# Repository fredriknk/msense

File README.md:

# Methanesense

 <!-- 3D rendered pretty view -->

Open Source hardware kicad source files for a NRF9160 based methane sensor utilizing MOX sensor.

Low power design with about 60ua average current consumption measuring Methane, temp, pressure and humidity every 30 seconds, averaging values over 5 minute samples, and transmitting 11 readings every 55 minutes. estimated battery life is 4.5 years from a 3200mah  18650 liion cell

It has an option for a GPS if necessary, but this will cause reduced battery life. 

[Assembly IBOM](https://htmlpreview.github.io/?https://raw.githubusercontent.com/fredriknk/Methanesense/main/DOCUMENTATION/ibom.html) <!-- Interactive BOM PDF -->

[PCB layout](./DOCUMENTATION/Methanesense_board_prints.pdf) <!-- PDFs of boards -->

[SCHEMATIC](./DOCUMENTATION/Methanesense_schematic.pdf) <!-- Schematic PDFs -->

## FRONT

## BACK

## SIDE

## Enclosure
Enclosure proposal. Simple 3d printed design snap lock, potential for epoxy fill for moisture resistance. But for now i just coat them in PLASTIK 70 conformal coating by Kontakt Chemie. DO REMEMBER TO SEAL SENSOR HOLES!!!

When 3d printing the enclosure, modify the two boxes in the sensor holes to be printed with gyroid infill with no walls or top/bottom to create the mesh. Enclosure files are in the [3D_MODEL](./3D_MODEL/) folder.

## Documentation

[NRF9160SOC](./DOCUMENTATION/Datasheets/nRF9160_PS_v2.0.pdf)

[ADC](./DOCUMENTATION/Datasheets/ads1113.pdf)

[Temp/press/humidity sensor](./DOCUMENTATION/Datasheets/bst-bme680-ds001.pdf)

[Powersupply PMIC](./DOCUMENTATION/Datasheets/nPM1300_PS_v1.0.pdf)

[MOX Sensor](./DOCUMENTATION/Datasheets/tgs8410_product_infomation(en)_rev05.pdf)

# Before major commmits
Remember to run generate_outputs.bat/sh
to update the outputs and pictures.
readmetemplate

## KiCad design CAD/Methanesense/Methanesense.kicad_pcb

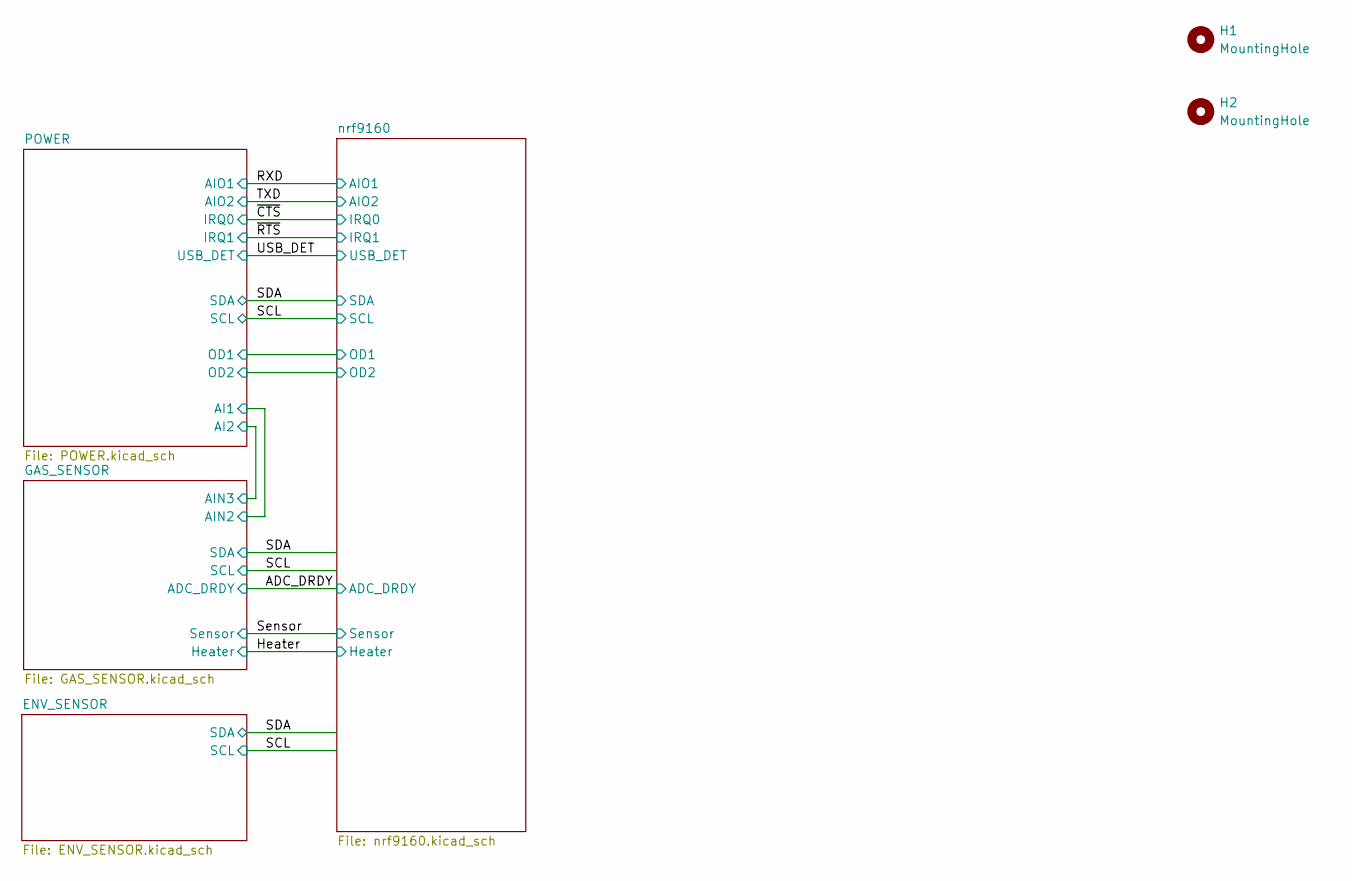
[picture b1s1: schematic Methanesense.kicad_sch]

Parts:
H1, H2: MountingHole; MountingHole_2.2mm_M2

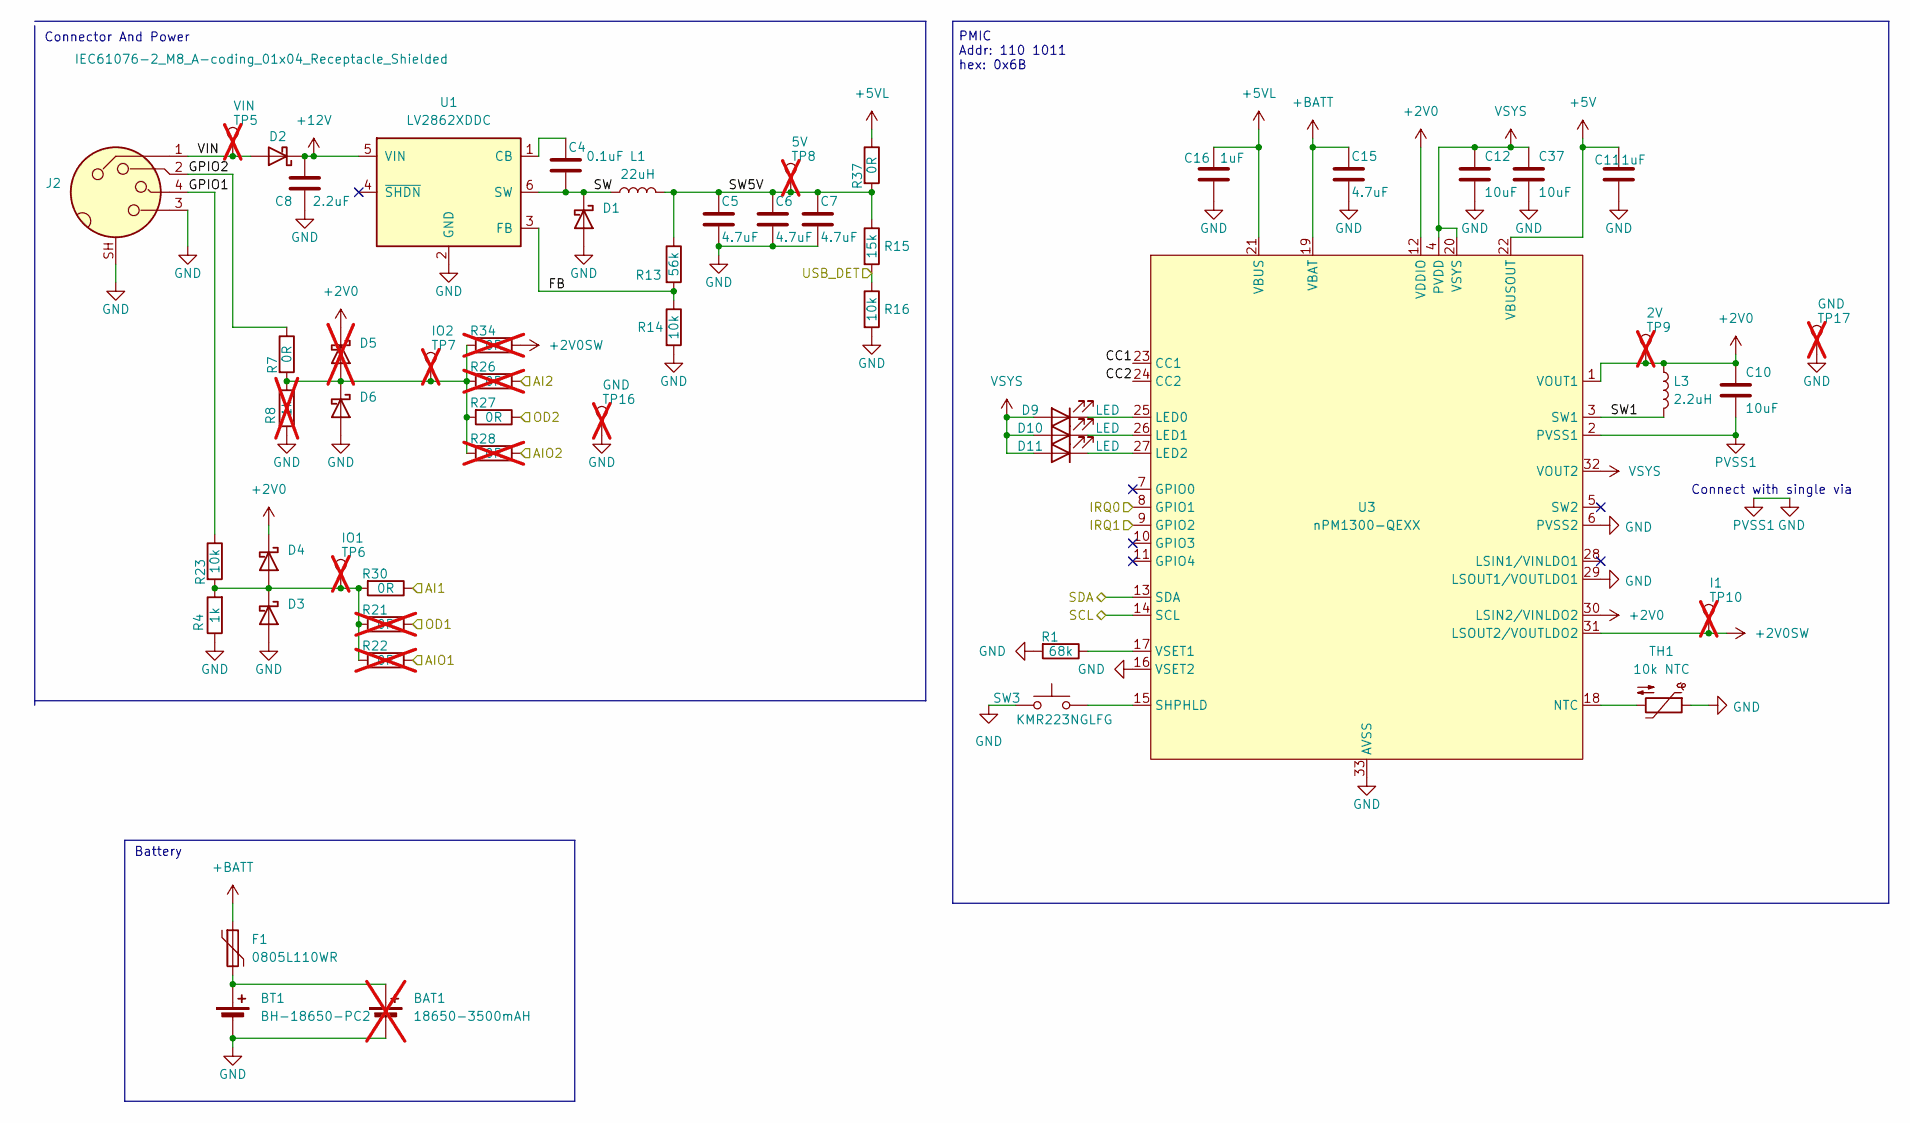
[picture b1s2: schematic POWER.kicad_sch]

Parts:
BAT1: 18650-3500mAH; not fitted
BT1: BH-18650-PC2; BatteryHolder_MPD_BH-18650-PC2; MPN BH-18650-PC2
C4: 0.1uF; C_0603_1608Metric
C5, C6, C7, C15: 4.7uF; C_0603_1608Metric
C8: 2.2uF; C_0805_2012Metric
C10, C12, C37: 10uF; C_0805_2012Metric
C11, C16: 1uF; C_0603_1608Metric
D1, D2: MSS1P3L-M3/89A; D_MicroSMP_AK; MPN MSS1P3L-M3/89A
D3, D4, D6: SD0603S040S0R2; D_0603_1608Metric; MPN SD0603S040S0R2
D5: SD0603S040S0R2; D_0603_1608Metric; MPN SD0603S040S0R2; not fitted
D9, D10, D11: LED; LED_0603_1608Metric; MPN LG L29K-G2J1-24-Z
F1: 0805L110WR; Fuse_0805_2012Metric; MPN 0805L110WR
J2: IEC61076-2_M8_A-coding_01x04_Receptacle_Shielded; STEWART_SS-12800-004_M8_04_Socket_Right_Angle; MPN SS-12800-004
L1: 22uH; L_Abracon_AMDLA4020S; MPN AMDLA4020S-220MT
L3: 2.2uH; L_1008_2520Metric; MPN CVH252009-2R2M
R1: 68k; R_0603_1608Metric
R4: 1k; R_0603_1608Metric
R7, R27, R30, R37: 0R; R_0603_1608Metric
R8: 1k; R_0603_1608Metric; not fitted
R13: 56k; R_0603_1608Metric
R14, R16, R23: 10k; R_0603_1608Metric
R15: 15k; R_0603_1608Metric
R21, R22, R26, R28, R34: 0R; R_0603_1608Metric; not fitted
SW3: KMR223NGLFG; SW_Push_1P1T_NO_CK_KMR2; MPN KMR223GLFG
TH1: 10k NTC; R_0603_1608Metric; MPN NTCG163JF103FT1
TP5: VIN; TestPoint_Pad_D1.0mm; not fitted
TP6: IO1; TestPoint_Pad_D1.0mm; not fitted
TP7: IO2; TestPoint_Pad_D1.0mm; not fitted
TP8: 5V; TestPoint_Pad_D1.0mm; not fitted
TP9: 2V; TestPoint_Pad_D1.0mm; not fitted
TP10: I1; TestPoint_Pad_D1.0mm; not fitted
TP16, TP17: GND; TestPoint_Pad_D1.0mm; not fitted
U1: LV2862XDDC; SOT-23-6; MPN LV2862XLVDDCR
U3: nPM1300-QEXX; QFN-32-1EP_5x5mm_P0.5mm_EP3.6x3.6mm_ThermalVias; MPN nPM1300-QEAA-R7

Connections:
+2V0: C10.1, D4.1 (K), D5.1 (K), L3.1, TP9.1, U3.1 (VOUT1), U3.12 (VDDIO), U3.30 (LSIN2/VINLDO2); also elsewhere on the board
+2V0SW: R34.1, TP10.1, U3.31 (LSOUT2/VOUTLDO2)
+5V: C11.1, U3.22 (VBUSOUT)
+5VL: C16.1, R37.1, U3.21 (VBUS)
+12V: C8.1, D2.1 (K), U1.5 (VIN); also elsewhere on the board
+BATT: C15.1, F1.1, U3.19 (VBAT); also elsewhere on the board
/GAS_SENSOR/AIN2: R30.1; also elsewhere on the board
/GAS_SENSOR/AIN3: R26.1; also elsewhere on the board
/POWER/CC1: U3.23 (CC1)
/POWER/CC2: U3.24 (CC2)
/POWER/FB: R13.2, R14.1, U1.3 (FB)
/POWER/GPIO1: J2.4, R23.1
/POWER/GPIO2: J2.2, R7.1
/POWER/OD1: R21.1; also elsewhere on the board
/POWER/OD2: R27.1; also elsewhere on the board
/POWER/SW: C4.2, D1.1 (K), L1.1, U1.6 (SW)
/POWER/SW1: L3.2, U3.3 (SW1)
/POWER/SW5V: C5.1, C6.1, C7.1, L1.2, R13.1, R15.1, R37.2, TP8.1
/POWER/VIN: D2.2 (A), J2.1, TP5.1
GND: BAT1.2 (-), BT1.2 (-), C5.2, C6.2, C7.2, C8.2, C10.2, C11.2, C12.2, C15.2, C16.2, C37.2, D1.2 (A), D3.2 (A), D6.2 (A), J2.3, J2.SH, R1.2, R4.1, R8.1, R14.2, R16.2, SW3.2, TH1.1, TP16.1, TP17.1, U1.2 (GND), U3.2 (PVSS1), U3.6 (PVSS2), U3.16 (VSET2), U3.29 (LSOUT1/VOUTLDO1), U3.33 (AVSS); also elsewhere on the board
unnamed: BAT1.1 (+), BT1.1 (+), F1.2
unnamed: D3.1 (K), D4.2 (A), R4.2, R21.2, R22.2, R23.2, R30.2, TP6.1
unnamed: D5.2 (A), D6.1 (K), R7.2, R8.2, R26.2, R27.2, R28.2, R34.2, TP7.1
unnamed: D9.1 (K), U3.25 (LED0)
unnamed: D10.1 (K), U3.26 (LED1)
unnamed: D11.1 (K), U3.27 (LED2)
unnamed: C4.1, U1.1 (CB)
unnamed: TH1.2, U3.18 (NTC)
unnamed: SW3.1, U3.15 (SHPHLD)
unnamed: R1.1, U3.17 (VSET1)
P0.05: R15.2, R16.1; also elsewhere on the board
P0.11: U3.8 (GPIO1); also elsewhere on the board
P0.12: U3.9 (GPIO2); also elsewhere on the board
P0.15/AIN2: R28.1; also elsewhere on the board
P0.16/AIN3: R22.1; also elsewhere on the board
P0.28: U3.13 (SDA); also elsewhere on the board
P0.29: U3.14 (SCL); also elsewhere on the board
VCC: C12.1, C37.1, D9.2 (A), D10.2 (A), D11.2 (A), U3.4 (PVDD), U3.20 (VSYS), U3.32 (VOUT2); also elsewhere on the board

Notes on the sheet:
Connect with single via
Addr: 110 1011 hex: 0x6B
Connector And Power
PMIC
Battery

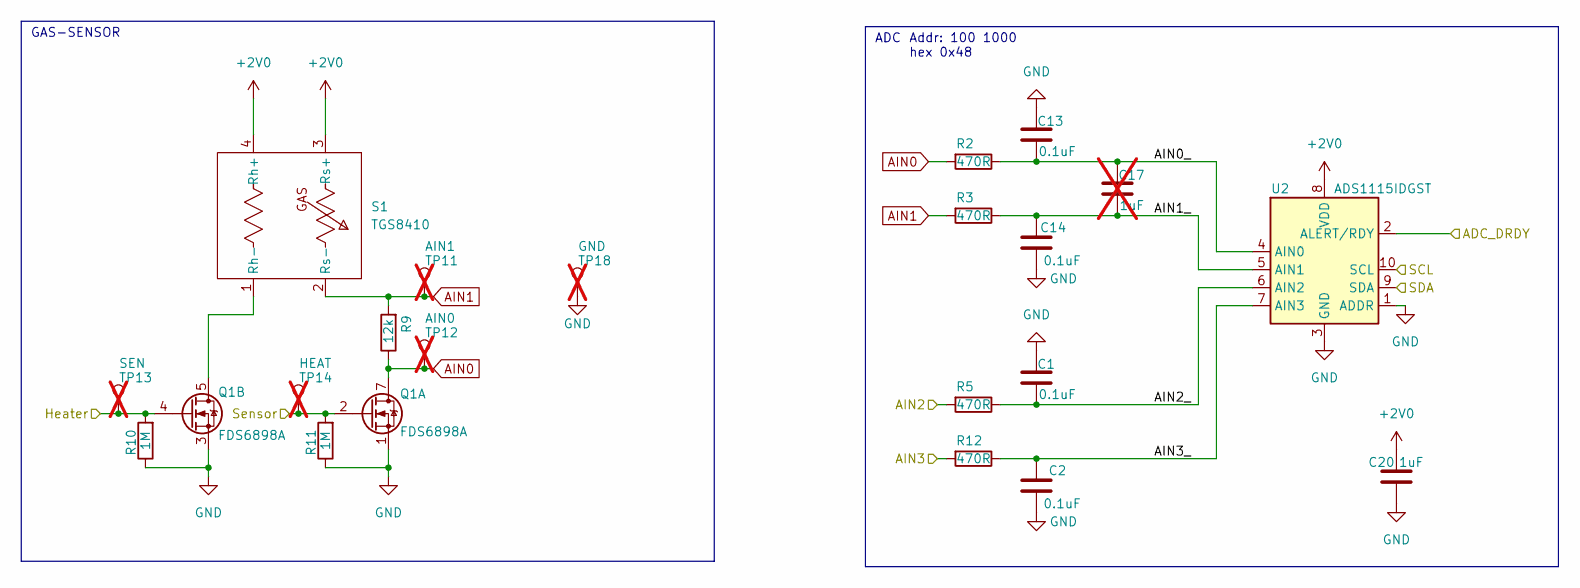
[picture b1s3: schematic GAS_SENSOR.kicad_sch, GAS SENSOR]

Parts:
C1, C2, C13, C14: 0.1uF; C_0603_1608Metric
C17: 1uF; C_0603_1608Metric; not fitted
C20: 1uF; C_0603_1608Metric
Q1: FDS6898A; SOIC-8_3.9x4.9mm_P1.27mm; MPN FDS6898A
R2, R3, R5, R12: 470R; R_0603_1608Metric
R9: 12k; R_0603_1608Metric
R10, R11: 1M; R_0603_1608Metric
S1: TGS8410; MPN TGS8410
TP11: AIN1; TestPoint_Pad_D1.0mm; not fitted
TP12: AIN0; TestPoint_Pad_D1.0mm; not fitted
TP13: SEN; TestPoint_Pad_D1.0mm; not fitted
TP14: HEAT; TestPoint_Pad_D1.0mm; not fitted
TP18: GND; TestPoint_Pad_D1.0mm; not fitted
U2: ADS1115IDGST; TSSOP-10_3x3mm_P0.5mm; MPN ADS1115IDGSR

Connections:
+2V0: C20.1, S1.3 (Rs+), S1.4 (Rh+), U2.8 (VDD); also elsewhere on the board
/GAS_SENSOR/AIN0_: C13.2, C17.1, R2.1, U2.4 (AIN0)
/GAS_SENSOR/AIN1_: C14.2, C17.2, R3.1, U2.5 (AIN1)
/GAS_SENSOR/AIN2: R5.2; also elsewhere on the board
/GAS_SENSOR/AIN2_: C1.2, R5.1, U2.6 (AIN2)
/GAS_SENSOR/AIN3: R12.2; also elsewhere on the board
/GAS_SENSOR/AIN3_: C2.2, R12.1, U2.7 (AIN3)
AIN0: Q1.7 (D1), Q1.8 (D1), R2.2, R9.1, TP12.1
AIN1: R3.2, R9.2, S1.2 (Rs-), TP11.1
GND: C1.1, C2.1, C13.1, C14.1, C20.2, Q1.1 (S1), Q1.3 (S2), R10.1, R11.1, TP18.1, U2.1 (ADDR), U2.3 (GND); also elsewhere on the board
unnamed: Q1.5 (D2), Q1.6 (D2), S1.1 (Rh-)
P0.26: U2.2 (ALERT/RDY); also elsewhere on the board
P0.27: Q1.2 (G1), R11.2, TP14.1; also elsewhere on the board
P0.28: U2.9 (SDA); also elsewhere on the board
P0.29: U2.10 (SCL); also elsewhere on the board
P0.31: Q1.4 (G2), R10.2, TP13.1; also elsewhere on the board

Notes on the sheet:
ADC
Addr: 100 1000 hex 0x48
GAS-SENSOR

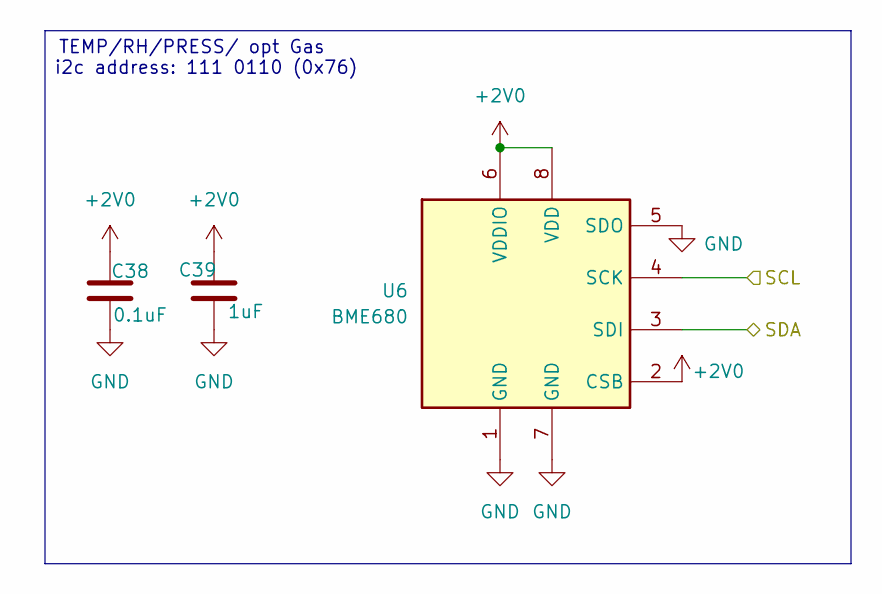
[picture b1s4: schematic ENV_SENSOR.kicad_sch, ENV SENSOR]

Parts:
C38: 0.1uF; C_0603_1608Metric
C39: 1uF; C_0603_1608Metric
U6: BME680; Bosch_LGA-8_3x3mm_P0.8mm_ClockwisePinNumbering; MPN BME680

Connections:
+2V0: C38.1, C39.1, U6.2 (CSB), U6.6 (VDDIO), U6.8 (VDD); also elsewhere on the board
GND: C38.2, C39.2, U6.1 (GND), U6.5 (SDO), U6.7 (GND); also elsewhere on the board
P0.28: U6.3 (SDI); also elsewhere on the board
P0.29: U6.4 (SCK); also elsewhere on the board

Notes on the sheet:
i2c address: 111 0110 (0x76)
TEMP/RH/PRESS/ opt Gas

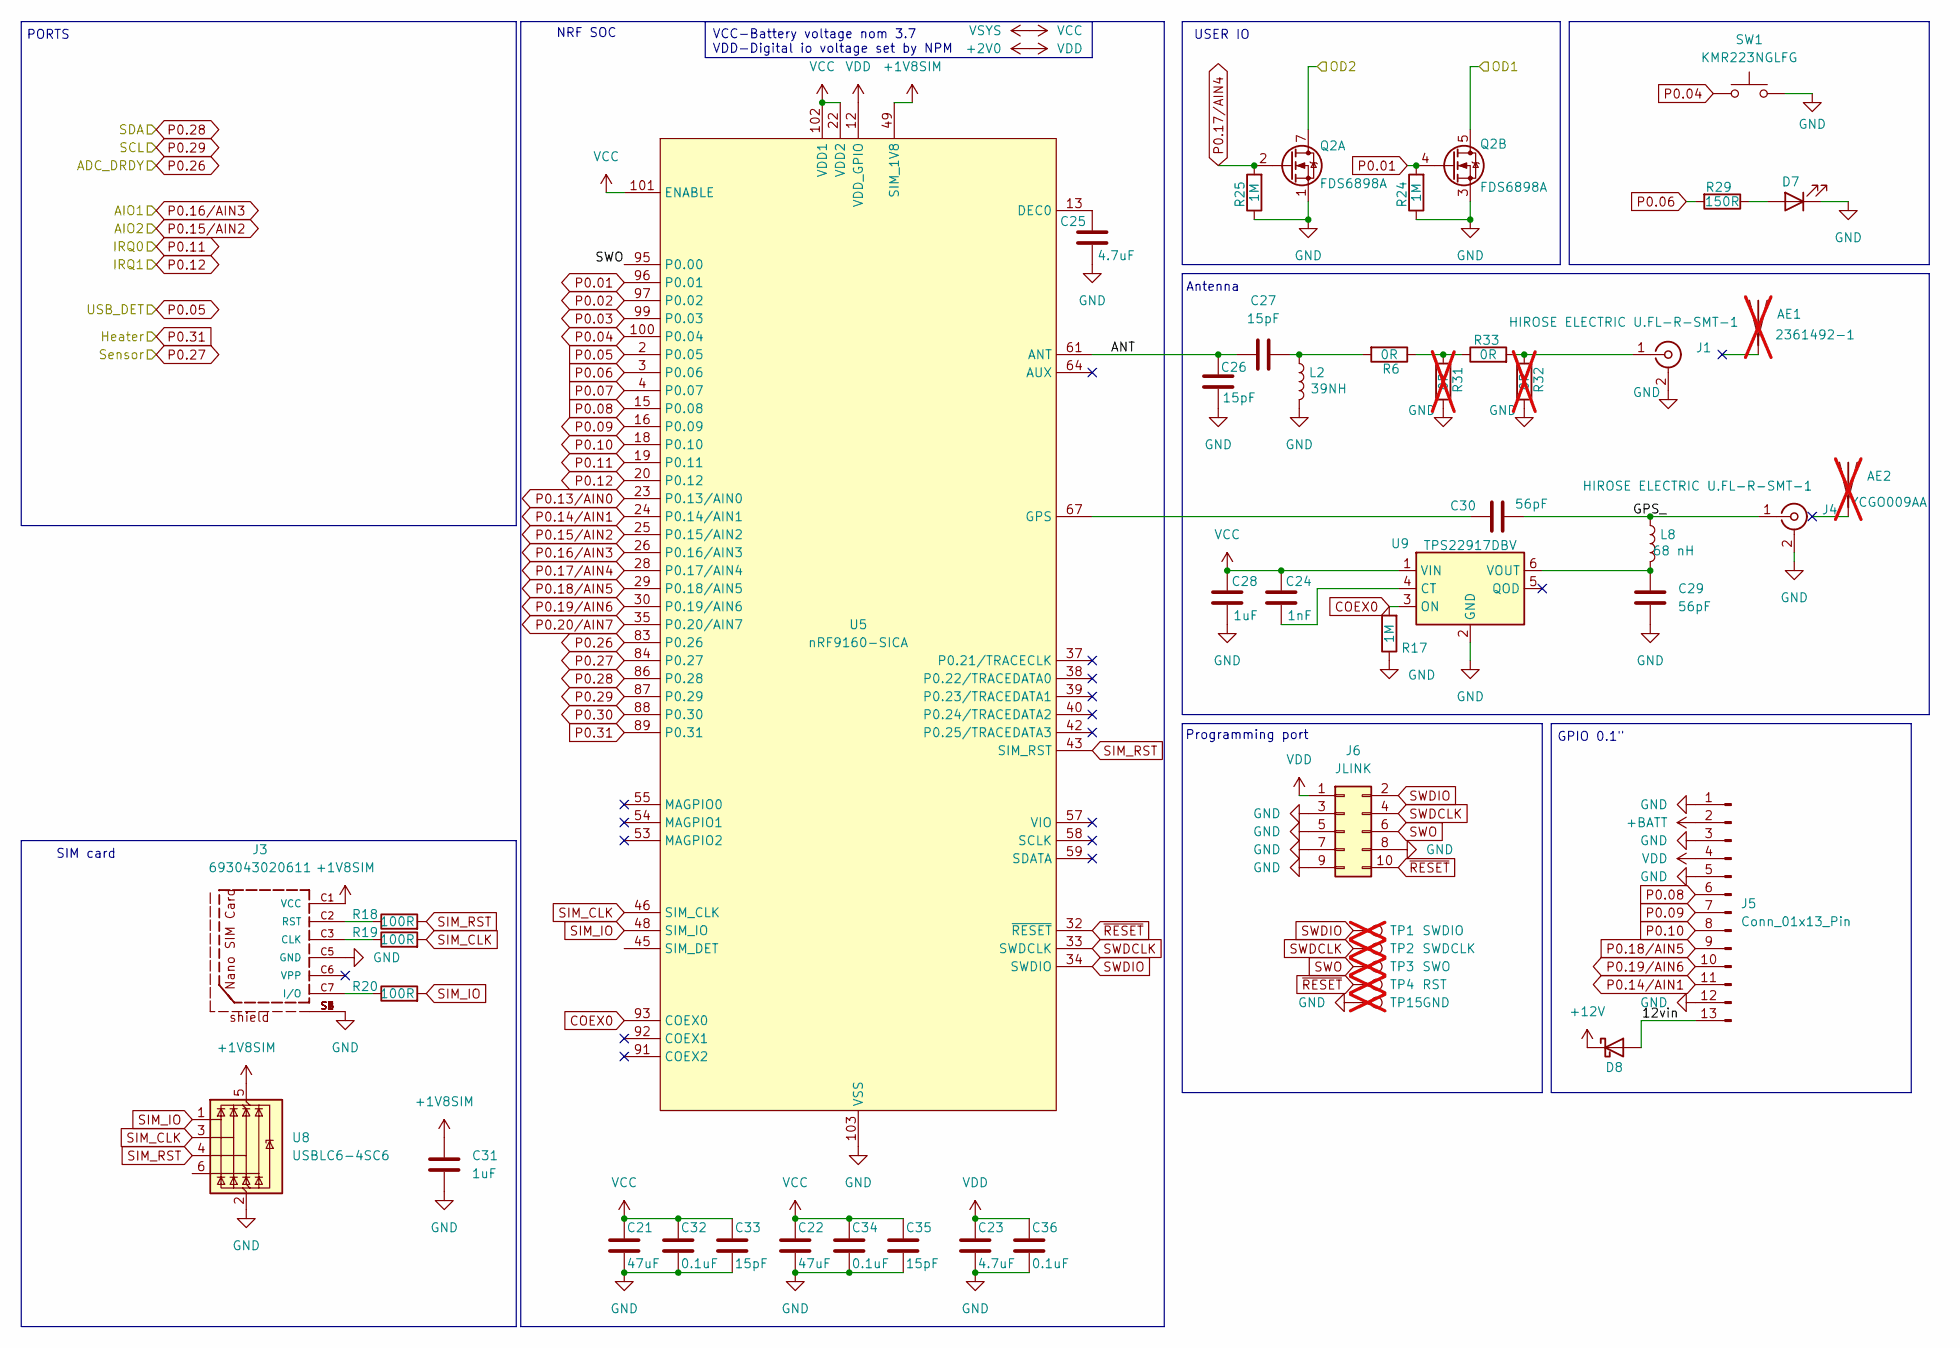
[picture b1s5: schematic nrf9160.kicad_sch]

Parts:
AE1: 2361492-1; MPN 2361492-1; not fitted
AE2: YCGO009AA; not fitted
C21, C22: 47uF; C_0805_2012Metric
C23, C25: 4.7uF; C_0603_1608Metric
C24: 1nF; C_0603_1608Metric
C26, C27, C33, C35: 15pF; C_0402_1005Metric_Sqr; MPN VJ0402D150FXCAJ
C28, C31: 1uF; C_0603_1608Metric
C29, C30: 56pF; C_0402_1005Metric_Sqr; MPN CBR04C560F1GAC
C32, C34, C36: 0.1uF; C_0603_1608Metric
D7: LG L29K-G2J1-24-Z; LED_0603_1608Metric; MPN LG L29K-G2J1-24-Z
D8: MSS1P3L-M3/89A; D_MicroSMP_AK; MPN MSS1P3L-M3/89A
J1, J4: HIROSE ELECTRIC U.FL-R-SMT-1; U.FL_Hirose_U.FL-R-SMT-1_Vertical; MPN U.FL-R-SMT-1
J3: 693043020611; PART-NUMBER 693043020611
J5: Conn_01x13_Pin; PinHeader_1x13_P2.54mm_Vertical
J6: JLINK; SEXY_pinpogo; MPN BD125-10-A-0305-0580-L-B
L2: 39NH; C_0402_1005Metric_Sqr; MPN LQW15AN39NJ8ZD
L8: 68 nH; C_0402_1005Metric_Sqr; MPN LQW15AN68NG0ZD
Q2: FDS6898A; SOIC-8_3.9x4.9mm_P1.27mm; MPN FDS6898A
R6, R33: 0R; R_0402_1005Metric
R17, R24, R25: 1M; R_0603_1608Metric
R18, R19, R20: 100R; R_0603_1608Metric
R29: 150R; R_0603_1608Metric
R31, R32: 0R; R_0402_1005Metric; not fitted
SW1: KMR223NGLFG; SW_Push_1P1T_NO_CK_KMR2; MPN KMR223GLFG
TP1: SWDIO; TestPoint_Pad_D1.0mm; not fitted
TP2: SWDCLK; TestPoint_Pad_D1.0mm; not fitted
TP3: SWO; TestPoint_Pad_D1.0mm; not fitted
TP4: RST; TestPoint_Pad_D1.0mm; not fitted
TP15: GND; TestPoint_Pad_D1.0mm; not fitted
U5: nRF9160-SICA; LGA_9160_16.0x10.5mm; MPN nRF9160-SICA-B1A-R7
U8: USBLC6-4SC6; SOT-23-6; MPN USBLC6-4SC6
U9: TPS22917DBV; SOT-23-6; MPN TPS22917DBVR

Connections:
+1V8SIM: C31.1, J3.C1 (VCC), U5.49 (SIM_1V8), U8.5 (VBUS)
+2V0: C23.1, C36.1, J5.4, J6.1, U5.12 (VDD_GPIO); also elsewhere on the board
+12V: D8.1 (K); also elsewhere on the board
+BATT: J5.2; also elsewhere on the board
/POWER/OD1: Q2.5 (D2), Q2.6 (D2); also elsewhere on the board
/POWER/OD2: Q2.7 (D1), Q2.8 (D1); also elsewhere on the board
/nrf9160/12vin: D8.2 (A), J5.13
/nrf9160/ANT: C26.1, C27.1, U5.61 (ANT)
/nrf9160/GPS_: C30.2, J4.1 (In), L8.1
COEX0: R17.2, U5.93 (COEX0), U9.3 (ON)
GND: C21.2, C22.2, C23.2, C25.2, C26.2, C28.2, C29.2, C31.2, C32.2, C33.2, C34.2, C35.2, C36.2, D7.1 (K), J1.2 (Ext), J3.C5 (GND), J3.S1, J3.S2, J3.S3, J3.S4, J3.S5, J3.S6, J4.2 (Ext), J5.1, J5.3, J5.5, J5.12, J6.3, J6.5, J6.7, J6.8, J6.9, L2.2, Q2.1 (S1), Q2.3 (S2), R17.1, R24.1, R25.1, R31.2, R32.2, SW1.2, TP15.1, U5.1 (GND_Shield), U5.5 (GND_Shield), U5.6 (GND_Shield), U5.7 (GND_Shield), U5.8 (GND_Shield), U5.9 (GND_Shield), U5.11 (GND_Shield), U5.14 (GND_Shield), U5.17 (GND_Shield), U5.21 (GND_Shield), U5.27 (GND_Shield), U5.31 (GND_Shield), U5.36 (GND_Shield), U5.41 (GND_Shield), U5.44 (GND_Shield), U5.47 (GND_Shield), U5.50 (GND_Shield), U5.52 (GND_Shield), U5.56 (GND_Shield), U5.60 (GND_Shield), U5.62 (GND_Shield), U5.63 (GND_Shield), U5.65 (GND_Shield), U5.66 (GND_Shield), U5.68 (GND_Shield), U5.69 (GND_Shield), U5.72 (GND_Shield), U5.74 (GND_Shield), U5.75 (GND_Shield), U5.76 (GND_Shield), U5.77 (GND_Shield), U5.78 (GND_Shield), U5.79 (GND_Shield), U5.80 (GND_Shield), U5.81 (GND_Shield), U5.82 (GND_Shield), U5.85 (GND_Shield), U5.90 (GND_Shield), U5.94 (GND_Shield), U5.98 (GND_Shield), U5.103 (VSS), U8.2 (GND), U9.2 (GND); also elsewhere on the board
unnamed: C27.2, L2.1, R6.2
unnamed: D7.2 (A), R29.1
unnamed: J1.1 (In), R32.1, R33.2
unnamed: J3.C3 (CLK), R19.1
unnamed: J3.C7 (I/O), R20.1
unnamed: J3.C2 (RST), R18.1
unnamed: R6.1, R31.1, R33.1
unnamed: C25.1, U5.13 (DEC0)
unnamed: C30.1, U5.67 (GPS)
unnamed: C24.2, U9.4 (CT)
unnamed: C29.1, L8.2, U9.6 (VOUT)
P0.01: Q2.4 (G2), R24.2, U5.96 (P0.01)
P0.02: U5.97 (P0.02)
P0.03: U5.99 (P0.03)
P0.04: SW1.1, U5.100 (P0.04)
P0.05: U5.2 (P0.05); also elsewhere on the board
P0.06: R29.2, U5.3 (P0.06)
P0.07: U5.4 (P0.07)
P0.08: J5.6, U5.15 (P0.08)
P0.09: J5.7, U5.16 (P0.09)
P0.10: J5.8, U5.18 (P0.10)
P0.11: U5.19 (P0.11); also elsewhere on the board
P0.12: U5.20 (P0.12); also elsewhere on the board
P0.13/AIN0: U5.23 (P0.13/AIN0)
P0.14/AIN1: J5.11, U5.24 (P0.14/AIN1)
P0.15/AIN2: U5.25 (P0.15/AIN2); also elsewhere on the board
P0.16/AIN3: U5.26 (P0.16/AIN3); also elsewhere on the board
P0.17/AIN4: Q2.2 (G1), R25.2, U5.28 (P0.17/AIN4)
P0.19/AIN6: J5.10, U5.30 (P0.19/AIN6)
P0.20/AIN7: U5.35 (P0.20/AIN7)
P0.26: U5.83 (P0.26); also elsewhere on the board
P0.27: U5.84 (P0.27); also elsewhere on the board
P0.28: U5.86 (P0.28); also elsewhere on the board
P0.29: U5.87 (P0.29); also elsewhere on the board
P0.30: U5.88 (P0.30)
P0.31: U5.89 (P0.31); also elsewhere on the board
SIM_CLK: R19.2, U5.46 (SIM_CLK), U8.3 (I/O2)
SIM_IO: R20.2, U5.48 (SIM_IO), U8.1 (I/O1)
SIM_RST: R18.2, U5.43 (SIM_RST), U8.4 (I/O3)
SWDCLK: J6.4, TP2.1, U5.33 (SWDCLK)
SWDIO: J6.2, TP1.1, U5.34 (SWDIO)
SWO: J6.6, TP3.1, U5.95 (P0.00)
VCC: C21.1, C22.1, C24.1, C28.1, C32.1, C33.1, C34.1, C35.1, U5.22 (VDD2), U5.101 (ENABLE), U5.102 (VDD1), U9.1 (VIN); also elsewhere on the board
~RESET: J6.10, TP4.1, U5.32 (~RESET)

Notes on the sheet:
Programming port
NRF SOC
USER IO
PORTS
SIM card
Antenna
GPIO 0.1"
VCC-Battery voltage nom 3.7 VDD-Digital io voltage set by NPM

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
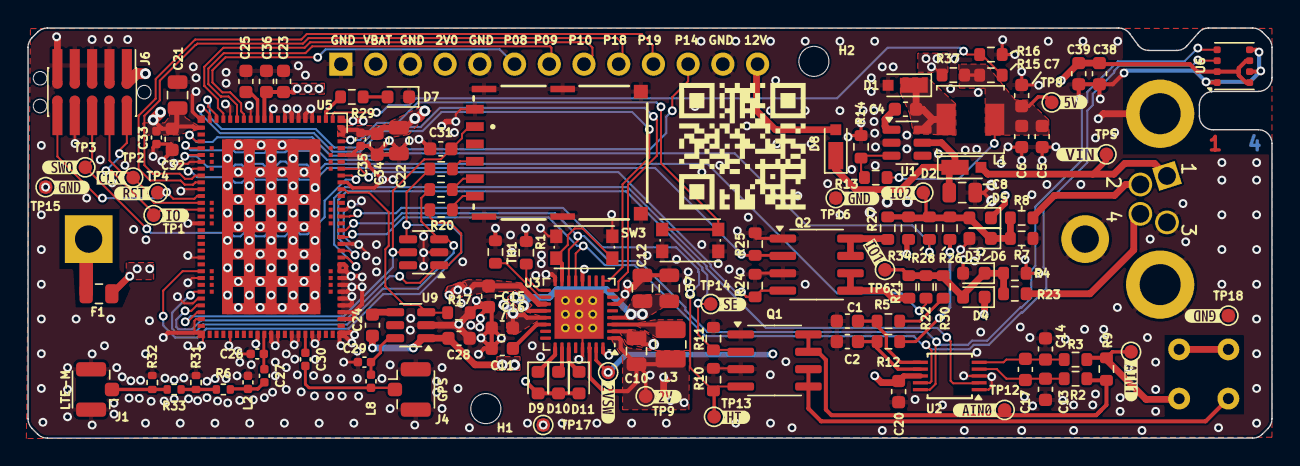
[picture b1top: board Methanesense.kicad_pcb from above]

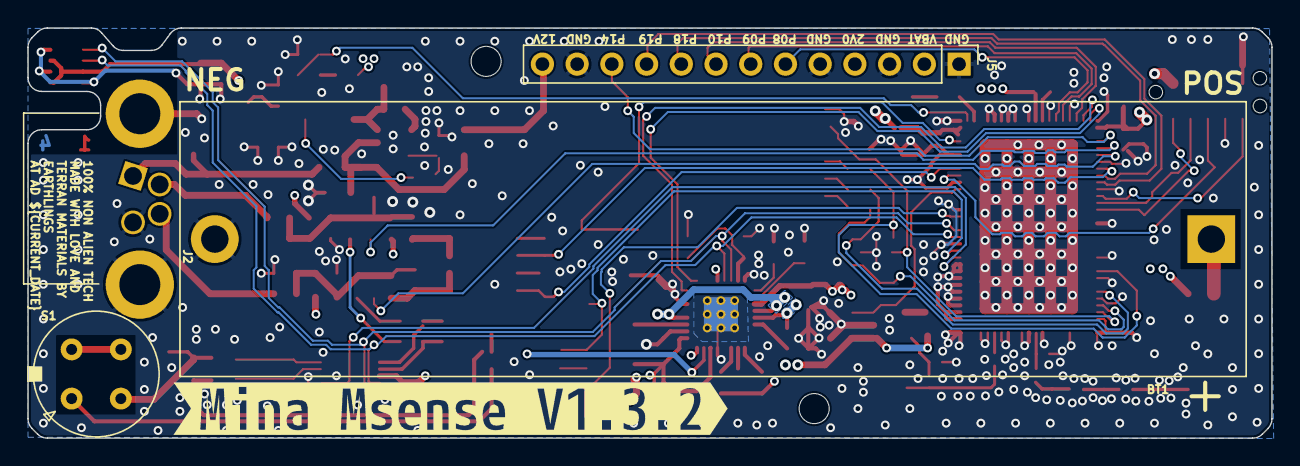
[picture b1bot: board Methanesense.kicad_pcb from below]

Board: 4 copper layers, 91.0 x 30.0 mm, 144 parts (5 on the bottom side), 79 nets.

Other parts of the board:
kibuzzard-680A1FD4: G***; kibuzzard-680A1FD4
kibuzzard-680B6FC7: G***; kibuzzard-680B6FC7
kibuzzard-680B70A9: G***; kibuzzard-680B70A9
kibuzzard-680B70C8: G***; kibuzzard-680B70C8
kibuzzard-680B70F6: G***; kibuzzard-680B70F6
kibuzzard-680B71B4, kibuzzard-680B71B4#2: G***; kibuzzard-680B71B4
kibuzzard-680B72A0: G***; kibuzzard-680B72A0
kibuzzard-680B72CB: G***; kibuzzard-680B72CB
kibuzzard-680B72EC: G***; kibuzzard-680B72EC
kibuzzard-680B73BF: G***; kibuzzard-680B73BF
kibuzzard-680B73D9: G***; kibuzzard-680B73D9
kibuzzard-680B701D: G***; kibuzzard-680B701D
kibuzzard-680B712B: G***; kibuzzard-680B712B
kibuzzard-680B714A: G***; kibuzzard-680B714A
kibuzzard-680B715D: G***; kibuzzard-680B715D
kibuzzard-680B7297: G***; kibuzzard-680B7297
kibuzzard-680B7325: G***; kibuzzard-680B7325

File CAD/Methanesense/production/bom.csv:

Designator,Footprint,Quantity,Value,LCSC Part #
AE1,XCVR_NN02-220,1,NN02-220,NN02-220
"C1, C2",0603,2,1.7pF,GJM1555C1H1R7WB01
"C10, C12, C37",0805,3,10uF,
"C11, C20, C28, C31, C39, C7, C8, C9",0603,8,1uF,
"C13, C14, C19, C32, C34, C36, C38",0603,7,0.1uF,
"C21, C22",0805,2,47uF,
"C23, C25",0603,2,4.7uF,
C24,0603,1,1nF,
"C26, C27, C33, C35",0402,4,15pF,GJM0335C1E150GB01D
"C29, C30",0402,2,56pF,CBR04C560F1GAC
"C3, C6",0603,2,47pF,
C4,0603,1,8.5pF,GJM1555C1H8R5WB01
"D10, D11, D5, D6, D9",0603,5,LED,LG L29K-G2J1-24-Z
F1,0805,1,0805L110WR,0805L110WR
J1,USB_C_Receptacle_HCTL_HC-TYPE-C-16P-01A,1,USB_C_Receptacle_USB2.0_14P,12402012E212A
J3,693043020611,1,693043020611,693043020611
J4,U.FL_Hirose_U.FL-R-SMT-1_Vertical,1,HIROSE ELECTRIC U.FL-R-SMT-1,U.FL-R-SMT-1
L1,0603,1,2.3nH,LQW15AN2N3G80
L2,0402,1,39NH,LQW15AN39NJ8ZD
L3,1008,1,2.2uH,CVH252009-2R2M
L5,0603,1,7.5NH,LQW15AN7N5G80
L6,0603,1,1.6nH,LQW15AN1N6C80
L8,0402,1, 68 nH ,LQW15AN68NG0ZD
"Q1, Q2",SOIC-8_3.9x4.9mm_P1.27mm,2,FDS6898A,FDS6898A
R1,0603,1,68k,
"R10, R11, R17, R24, R25",0603,5,1M,
"R18, R19, R20, R22, R23",0603,5,100R,
"R2, R3",0603,2,470R,
R26,0603,1,1k,
R5,0603,1,0R,
"SW1, SW3",SW_Push_1P1T_NO_CK_KMR2,2,KMR223NGLFG,KMR223NGLFG
SW4,SW_DPDT_CK_JS202011JCQN,1,JS202011JCQN,JS202011JCQN
TH1,0603,1,10k NTC,10k NTC
U2,TSSOP-10_3x3mm_P0.5mm,1,ADS1115IDGS,ADS1115IDGS
U3,QFN-32-1EP_5x5mm_P0.5mm_EP3.6x3.6mm,1,nPM1300-QEXX,nPM1300-QEAA-R7
U4,SOT-23-5,1,AP7331-20WG-7,AP7331-20WG-7
U5,LGA_9160_16.0x10.5mm,1,nRF9160-SICA,nRF9160-SICA
U6,Bosch_LGA-8_3x3mm_P0.8mm_ClockwisePinNumbering,1,BME680,BME680
U7,QFN-16-1EP_4x4mm_P0.65mm_EP2.1x2.1mm,1,FT230XQ,FT230XQ
U8,SOT-23-6,1,USBLC6-4SC6,USBLC6-4SC6
U9,SOT-23-6,1,TPS22917DBV,TPS22917DBVR

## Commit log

2024-07-05 NRF9160
2024-08-01 Allmost there
2024-08-05 NRF footprint change
2024-08-12 Rev 2.0.0
2024-08-12 Readme update
2025-04-16 rev 1.2
2025-04-25 Feat: Rev 1.3
2025-04-28 Feat: Cleaning up schems
2025-08-20 Feat: Prettified repo Readme
2025-08-21 Fix: Path Locations
2025-08-21 Fix: Trying to correct lower case error
2025-08-21 Fix: Now with large M
2025-08-21 Fix: CI Push
2025-08-21 Fix: Ibom work
2025-08-21 Oups
2025-08-21 There
2025-08-22 Fix: Update battery size README.md
